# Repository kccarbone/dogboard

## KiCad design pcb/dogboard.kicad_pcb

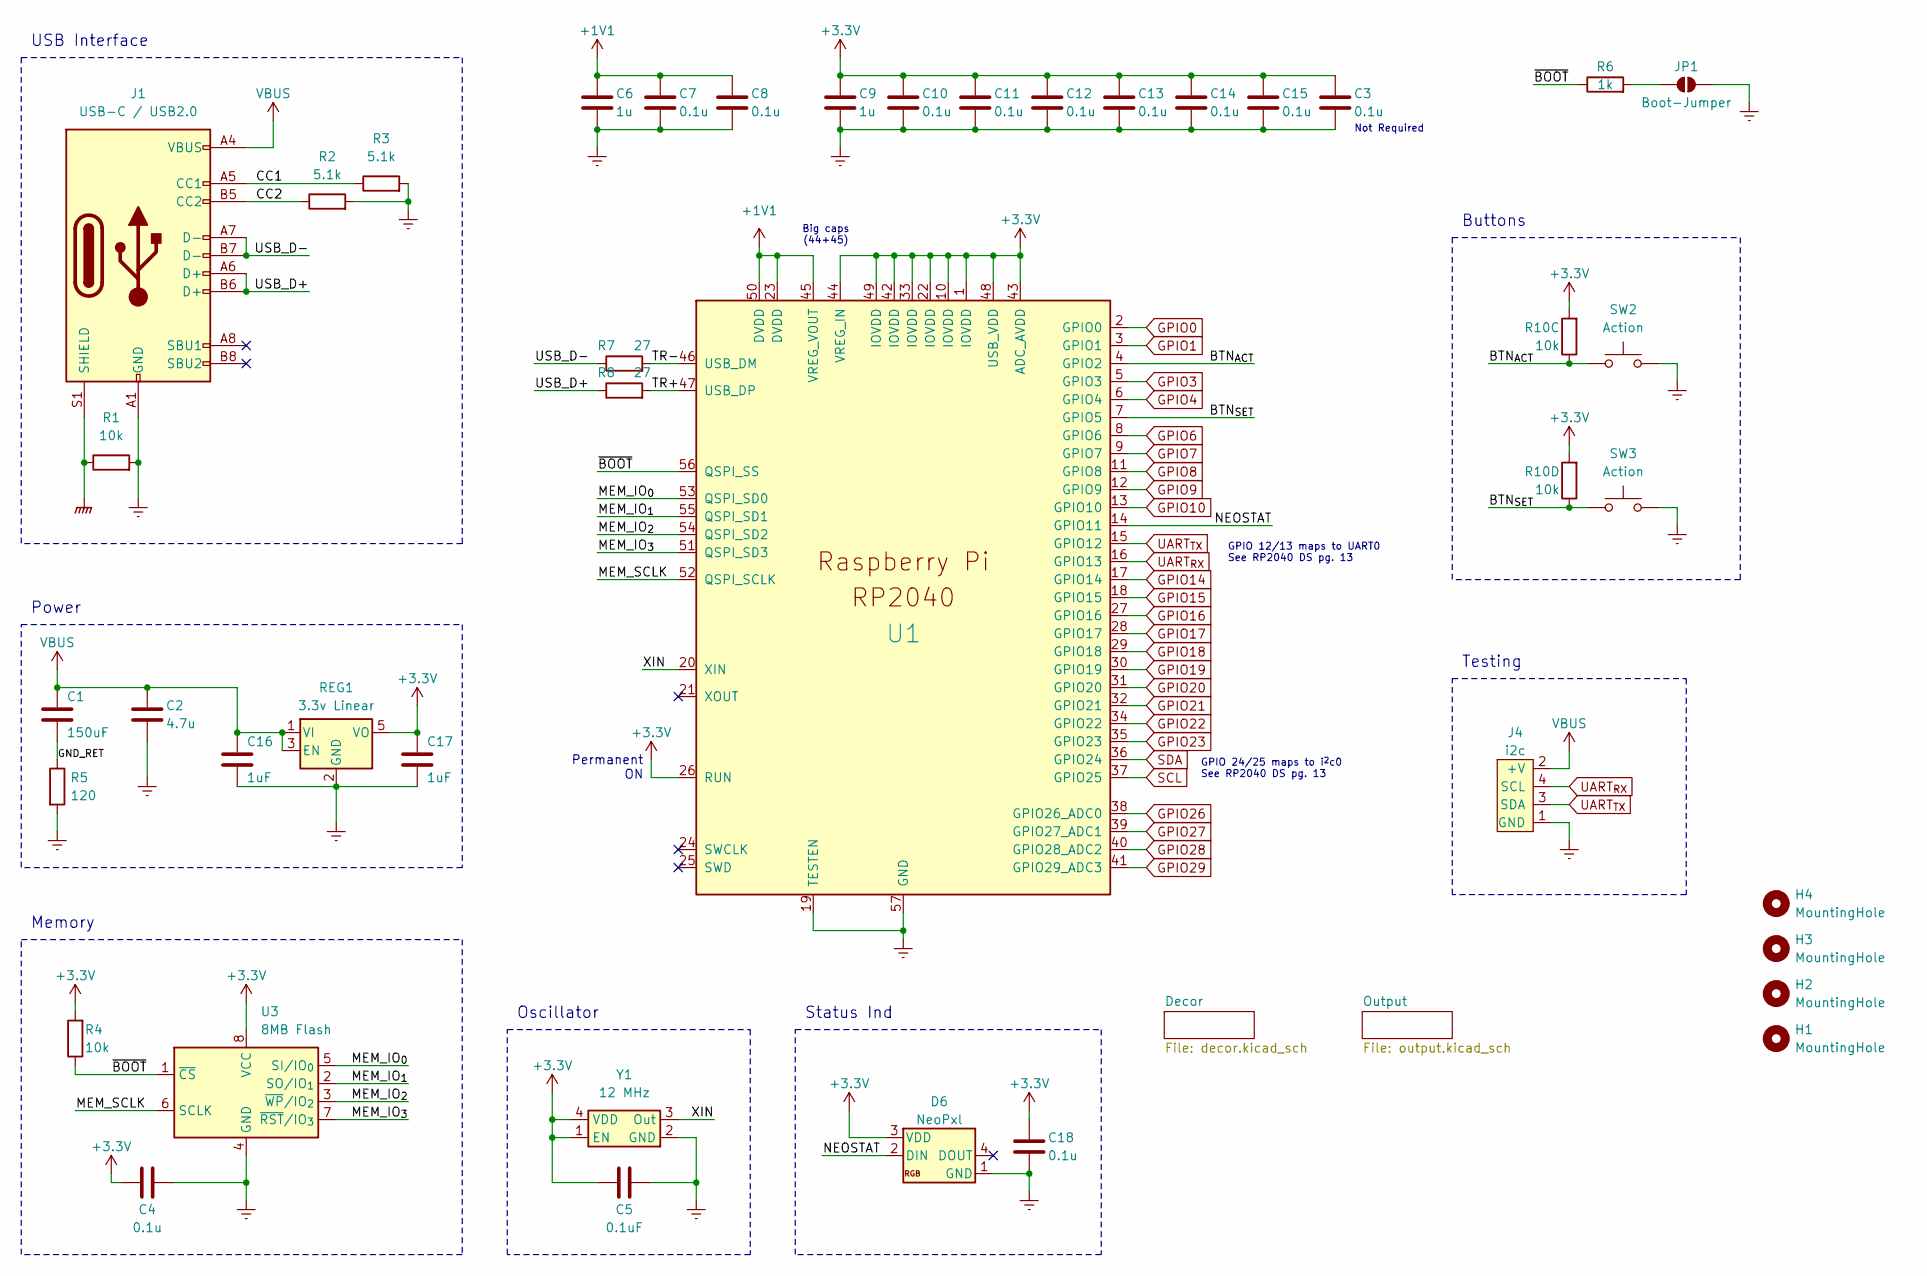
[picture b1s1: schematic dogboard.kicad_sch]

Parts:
C1: 150uF; CAP_Tantalum_2312
C2: 4.7u; CAP_0805_NoKeepout
C3, C7, C8, C10, C11, C12, C13, C14, C15, C18: 0.1u; CAP_0402_HandSolder
C4: 0.1u; CAP_0603_HandSolder
C5: 0.1uF; CAP_0603_HandSolder
C6, C9: 1u; CAP_0603_HandSolder
C16, C17: 1uF; CAP_0805_HandSolder
D6: NeoPxl; LED_NeoPixel_0606
H1, H2, H3, H4: MountingHole; MountingHole_M2.5
J1: USB-C / USB2.0; USB_C_Receptacle_SMD_GCT
J4: i2c; conn_1x04mp_JST_SH_Micro_P1.00mm_Horizontal
JP1: Boot-Jumper; Jumper_Open_SMD_3.5mm
R1: 10k; R_1206_HandSolder
R2, R3: 5.1k; R_0603_HandSolder
R4: 10k; R_0603_HandSolder
R5: 120; R_1206_HandSolder
R6: 1k; R_0603_HandSolder
R7, R8: 27; R_0402_HandSolder
R10: 10k; R_Array_4x1206_Convex
REG1: 3.3v Linear; reg_SMD_SOT-25
SW2, SW3: Action; button_SMD_PTS810
U1: RP2040; RP2040_QFN-56
U3: 8MB Flash; flash_SMD_XSON-8_4x4mm
Y1: 12 MHz; XO_Osc_4-SMD_3.2x2.5

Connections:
+1V1: C6.1, C7.1, C8.1, U1.23 (DVDD), U1.45 (VREG_VOUT), U1.50 (DVDD)
+3.3V: C3.1, C4.2, C5.1, C9.1, C10.1, C11.1, C12.1, C13.1, C14.1, C15.1, C17.1, C18.1, D6.3 (VDD), R4.2, R10.6, R10.8, REG1.5 (VO), U1.1 (IOVDD), U1.10 (IOVDD), U1.22 (IOVDD), U1.26 (RUN), U1.33 (IOVDD), U1.42 (IOVDD), U1.43 (ADC_AVDD), U1.44 (VREG_IN), U1.48 (USB_VDD), U1.49 (IOVDD), U3.8 (VCC), Y1.1 (EN), Y1.4 (VDD); also elsewhere on the board
/BTN_{ACT}: R10.5, SW2.1, U1.4 (GPIO2)
/BTN_{SET}: R10.7, SW3.1, U1.7 (GPIO5)
/CC1: J1.A5 (CC1), R3.1
/CC2: J1.B5 (CC2), R2.1
/GND_RET: C1.2, R5.1
/MEM_IO_{0}: U1.53 (QSPI_SD0), U3.5 (SI/IO_{0})
/MEM_IO_{1}: U1.55 (QSPI_SD1), U3.2 (SO/IO_{1})
/MEM_IO_{2}: U1.54 (QSPI_SD2), U3.3 (~WP/IO_{2})
/MEM_IO_{3}: U1.51 (QSPI_SD3), U3.7 (~RST/IO_{3})
/MEM_SCLK: U1.52 (QSPI_SCLK), U3.6 (SCLK)
/NEOSTAT: D6.2 (DIN), U1.14 (GPIO11)
/TR+: R8.2, U1.47 (USB_DP)
/TR-: R7.2, U1.46 (USB_DM)
/USB_D+: J1.A6 (D+), J1.B6 (D+), R8.1
/USB_D-: J1.A7 (D-), J1.B7 (D-), R7.1
/XIN: U1.20 (XIN), Y1.3 (Out)
/~BOOT: R4.1, R6.1, U1.56 (QSPI_SS), U3.1 (~CS)
GNDPWR: J1.S1 (SHIELD), R1.1
GNDREF: C2.2, C3.2, C4.1, C5.2, C6.2, C7.2, C8.2, C9.2, C10.2, C11.2, C12.2, C13.2, C14.2, C15.2, C16.2, C17.2, C18.2, D6.1 (GND), J1.A1 (GND), J1.A12 (GND), J1.B1 (GND), J1.B12 (GND), J4.1 (GND), JP1.2 (B), R1.2, R2.2, R3.2, R5.2, REG1.2 (GND), SW2.2, SW3.2, U1.19 (TESTEN), U1.57 (GND), U3.4 (GND), Y1.2 (GND); also elsewhere on the board
GPIO0: U1.2 (GPIO0)
GPIO1: U1.3 (GPIO1)
GPIO3: U1.5 (GPIO3)
GPIO4: U1.6 (GPIO4)
GPIO6: U1.8 (GPIO6)
GPIO7: U1.9 (GPIO7)
GPIO8: U1.11 (GPIO8)
GPIO9: U1.12 (GPIO9)
GPIO10: U1.13 (GPIO10)
GPIO14: U1.17 (GPIO14)
GPIO15: U1.18 (GPIO15)
GPIO16: U1.27 (GPIO16)
GPIO17: U1.28 (GPIO17)
GPIO18: U1.29 (GPIO18)
GPIO19: U1.30 (GPIO19)
GPIO20: U1.31 (GPIO20)
GPIO21: U1.32 (GPIO21)
GPIO22: U1.34 (GPIO22)
GPIO23: U1.35 (GPIO23)
GPIO26: U1.38 (GPIO26_ADC0)
GPIO27: U1.39 (GPIO27_ADC1)
GPIO28: U1.40 (GPIO28_ADC2)
GPIO29: U1.41 (GPIO29_ADC3)
unnamed: JP1.1 (A), R6.2
SCL: U1.37 (GPIO25); also elsewhere on the board
SDA: U1.36 (GPIO24); also elsewhere on the board
UART_{RX}: J4.4 (SCL), U1.16 (GPIO13)
UART_{TX}: J4.3 (SDA), U1.15 (GPIO12)
VBUS: C1.1, C2.1, C16.1, J1.A4 (VBUS), J1.A9 (VBUS), J1.B4 (VBUS), J1.B9 (VBUS), J4.2 (+V), REG1.1 (VI), REG1.3 (EN); also elsewhere on the board

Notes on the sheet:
Big caps (44+45)
Testing
USB Interface
Power
GPIO 24/25 maps to i^{2}c0 See RP2040 DS pg. 13
Status Ind
Permanent ON
Oscillator
GPIO 12/13 maps to UART0 See RP2040 DS pg. 13
Memory
Buttons
Not Required

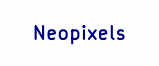
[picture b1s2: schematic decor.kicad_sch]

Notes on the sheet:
Neopixels

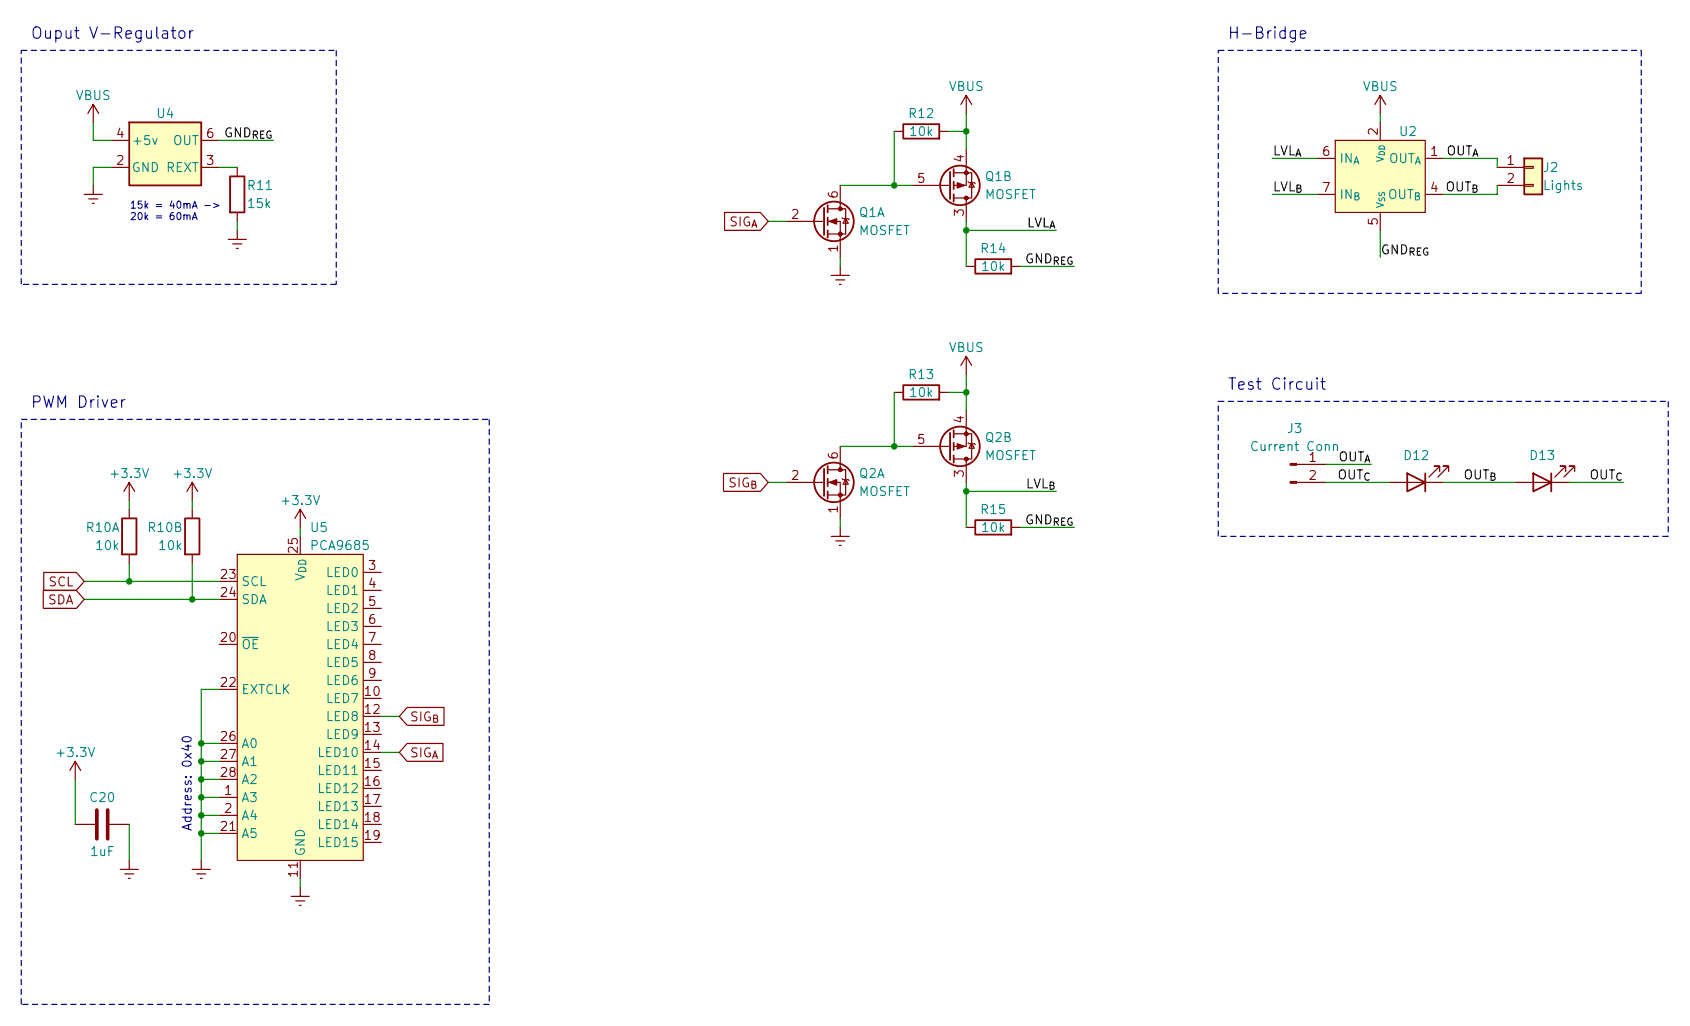
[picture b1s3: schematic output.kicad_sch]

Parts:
C20: 1uF; CAP_0603_HandSolder
D12, D13: MP-LED; LED_MP-Cathode_1113
J2: Lights; conn_1x02_JST_PH_P2.00mm_THT_Horizontal
J3: Current Conn; PinHeader_1x02_P2.54mm_Vertical
Q1, Q2: MOSFET; GenericIC_SOT-363
R10: 10k; R_Array_4x1206_Convex
R11: 15k; R_0805_HandSolder
R12, R13, R14, R15: 10k; R_0603_HandSolder
U2: L9110H; GenericIC_TH-DIP-8
U4: BCR430; BCR430_CC_LED_Driver
U5: PCA9685; GenericIC_VQFN-28-EP-6x6mm

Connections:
+3.3V: C20.1, R10.1, R10.3, U5.25 (V_{DD}); also elsewhere on the board
/Output/LVL_{A}: Q1.3 (D_{B}), R14.1, U2.6 (IN_{A})
/Output/LVL_{B}: Q2.3 (D_{B}), R15.1, U2.7 (IN_{B})
/Output/OUT_{A}: J2.1, J3.1, U2.1 (OUT_{A})
/Output/OUT_{B}: D12.1 (K), D13.2 (A), J2.2, U2.4 (OUT_{B})
/Output/OUT_{C}: D12.2 (A), D13.1 (K), J3.2
GNDREF: C20.2, Q1.1 (S_{A}), Q2.1 (S_{A}), R11.2, U4.2 (GND), U5.1 (A3), U5.2 (A4), U5.11 (GND), U5.21 (A5), U5.22 (EXTCLK), U5.26 (A0), U5.27 (A1), U5.28 (A2); also elsewhere on the board
unnamed: Q1.5 (G_{B}), Q1.6 (D_{A}), R12.1
unnamed: Q2.5 (G_{B}), Q2.6 (D_{A}), R13.1
unnamed: R11.1, U4.3 (REXT)
SCL: R10.2, U5.23 (SCL); also elsewhere on the board
SDA: R10.4, U5.24 (SDA); also elsewhere on the board
SIG_{A}: Q1.2 (G_{A}), U5.14 (LED10)
SIG_{B}: Q2.2 (G_{A}), U5.12 (LED8)
VBUS: Q1.4 (S_{B}), Q2.4 (S_{B}), R12.2, R13.2, U2.2 (V_{DD}), U2.3 (V_{DD}), U4.4 (+5v); also elsewhere on the board
V_{SS}: R14.2, R15.2, U2.5 (V_{SS}), U2.8 (V_{SS}), U4.6 (OUT)

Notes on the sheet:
H-Bridge
PWM Driver
Address: 0x40
Ouput V-Regulator
15k = 40mA -> 20k = 60mA
Test Circuit

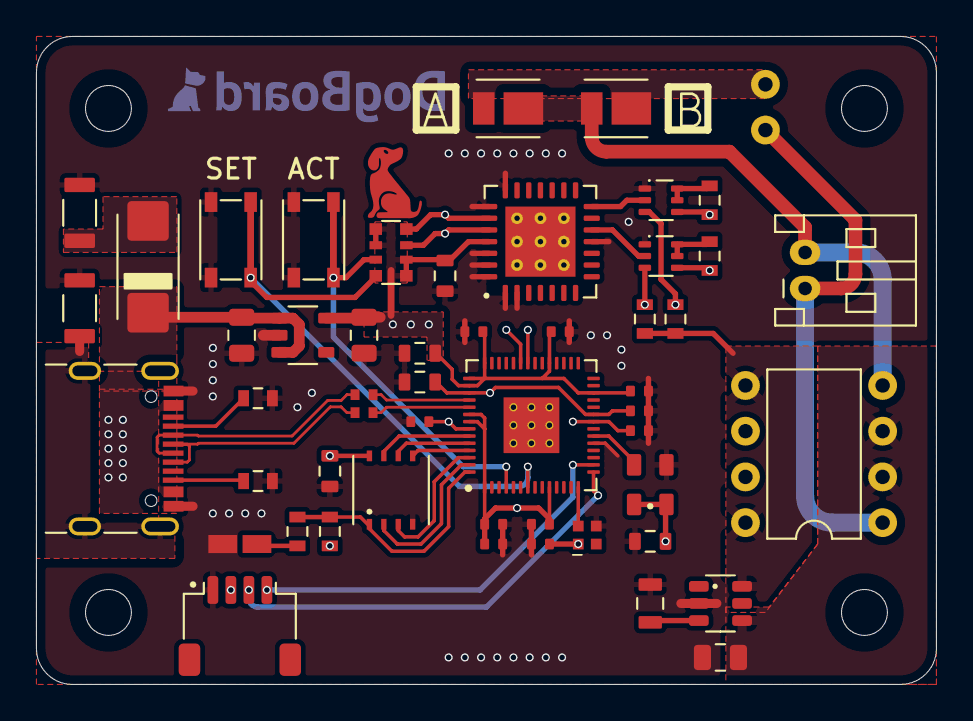
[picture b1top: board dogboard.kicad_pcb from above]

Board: 6 copper layers, 50.0 x 36.0 mm, 56 parts (0 on the bottom side), 38 nets.

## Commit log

2023-03-19 initial firmware upload
2023-04-06 added pcb project
2023-04-09 firmware updates
2024-03-10 pcb refactor
2024-03-11 rework power regulator
2024-04-13 PBC rev 2 beta-1
2024-06-02 PCB rev 2 beta-2
2025-01-11 dogboard-2b3
2025-02-14 pcb updates
2025-02-16 dogboard-2b4
2025-05-04 New board revision
